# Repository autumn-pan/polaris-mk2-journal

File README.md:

# Lepton Rocket
The Lepton Rocket is a TVC rocket that is capable of guiding itself using its thruster, as well as vertical landing using a second thruster. It requires no parachute or fins and is capable of self-stabilization using only gimballed motors and lands propulsively.

# Motivation
Our motivation for building this rocket stems from a deep passion for model rocketry and a will to learn and improve through this project. Building such a complicated rocket not only helps us learn and grow as people but also pushes technological boundaries we face today with innovative new solutions. Every step, from Kalman filters to thrust vectoring, offers unique challenges that serve as learning experiences. We hope that our work will go on to support other aspiring rocketeers through open sourcing and tutorials. Moreover, we are testing new methods of reversing exhaust jets and are testing materials in extreme environments. We hope that this research will inspire other projects that can make a real impact.

# Design

PCB

WIRING

CAD

# CAD Files
View the CAD files in ./cad, or preferably in the onshape document
[Link](https://cad.onshape.com/documents/b936ec593d2f13f8b4301d6a/w/959d82f8ce1a388125efc6ac/e/d0e27454aa34d56363c8f698)
# BOM -- Total Cost: $288.5, $307.25 after tax
| Name                          | Cost   | Link                                                                                                                                                                                                                                                                                                                                                      | Purpose                                           |
|-------------------------------|--------|------------------------------------------------------------------------------------------------------------------------------------------------------------------------------------------------------------------------------------------------------------------------------------------------------------------------------------------------------------|---------------------------------------------------|
| Teensy 4.1                    | 35.49  | [Link](https://www.amazon.com/PJRC-Cortex-M7-Processor-iMXRT1062-Without/dp/B088JY7P2H/ref=asc_df_B088JY7P2H?mcid=8ae789eb80d63b429a8b6233ef5751e7&hvocijid=17548775748303405856-B088JY7P2H-&hvexpln=73&tag=hyprod-20&linkCode=df0&hvadid=730312820598&hvpos=&hvnetw=g&hvrand=17548775748303405856&hvpone=&hvptwo=&hvqmt=&hvdev=c&hvdvcmdl=&hvlocint=&hvlocphy=9001697&hvtargid=pla-2281435177898&psc=1) | Processing information and running code          |
| Bosch Sensortec BMI088                        | 5.23   | [Link](https://www.digikey.com/en/products/detail/bosch-sensortec/BMI088/8634936)                                                                                                                                                                                                                                 | Reading inertial data                            |
| Bosch Sensortec BMP390                        | 3.15   | [Link](https://www.digikey.com/en/products/detail/bosch-sensortec/BMP390/16164577)                                                                                                                                                                                                                               | Reading altitude                                 |
| 2 WAGOs  (2601-1104)                     | 8.72   | [Link](https://www.digikey.com/en/products/detail/wago-corporation/2601-1104/17123797?gQT=1)                                                                                                                                                                                                                     | Connecting pyro channels                         |
| XT30U connector                        | 0.72   | [Link](https://www.tme.eu/en/details/xt30upb-m/dc-power-connectors/amass/?utm_source=octopart.com&utm_medium=cpc&utm_campaign=compare-2025-05-27)                                                                                                                                                                 | Connecting the battery                           |
| 8x Servo Pins    (G800W305018EU)         | 7.84   | [Link](https://www.digikey.com/en/products/detail/amphenol-icc-commercial-products-/G800W305018EU/13683151?gQT=1)                                                                                                                                                                                                 | Connecting the servo pins                        |
| 5x DMN1019UVT-7                     | 4.10   | [Link](https://www.digikey.com/en/products/detail/diodes-incorporated/DMN1019UVT-7/5126835)                                                                                                                                                                                                                       | Controlling pyro channels                        |
| Printed Circuit Board         | 50.00  | [Link](https://jlcpcb.com/)                                                                                                                                                                                                                                                                                       | Mounting flight computer devices on. We only ask that you pay for printing, shipping, and taxes on the raw circuit boards. We will try to fund the resistors, capacitors, etc. ourselves             |
| 3ml Syringes                  | 2.93  | [Link](https://www.aliexpress.us/item/3256806328171497.html?spm=a2g0o.productlist.main.1.413b734d9NaMbA&aem_p4p_detail=2025073016395111874069278487360002035883&algo_pvid=8ce5ca76-1fcf-42fd-9431-eb7cfd16bba9&algo_exp_id=8ce5ca76-1fcf-42fd-9431-eb7cfd16bba9-0&pdp_ext_f=%7B%22order%22%3A%22832%22%2C%22eval%22%3A%221%22%7D&pdp_npi=4%40dis!USD!2.60!2.60!!!18.56!18.56!%40210313e917539187916456686eafd5!12000037489056984!sea!US!0!ABX&curPageLogUid=oJgz2mSzbKY4&utparam-url=scene%3Asearch%7Cquery_from%3A&search_p4p_id=2025073016395111874069278487360002035883_1)                                                                                                                                                                                                                                                                        | Dampening landing legs                           |
| Brushless Motor               | 0.99   | [Link](https://www.aliexpress.us/item/3256806626806030.html?)                                                                                                                                                                                                                                                     | Driving the reaction wheel                       |
| Extension Cable               | 5.99   | [Link](https://www.amazon.com/FLY-RC-Connector-Extension-Brushless/dp/B0B12CFKNZ/ref=asc_df_B0B12CFKNZ?mcid=8e5db81149053e17aedeaeb54fc6da1f&hvocijid=2611908650921179939-B0B12CFKNZ-&hvexpln=73&tag=hyprod-20&linkCode=df0&hvadid=721245378154&hvpos=&hvnetw=g&hvrand=2611908650921179939&hvpone=&hvptwo=&hvqmt=&hvdev=c&hvdvcmdl=&hvlocint=&hvlocphy=9001697&hvtargid=pla-2281435177618&th=1) | Connecting the motor to the flight computer      |
| Set Screws 50pc 2cm 5mm       | 1.38   | [Link](https://www.aliexpress.us/item/2251832795980382.html?spm=a2g0o.productlist.main.11.4816cYVfcYVfrL&algo_pvid=4b71b07a-a4f2-45ce-9069-14c906ecce58&algo_exp_id=4b71b07a-a4f2-45ce-9069-14c906ecce58-10&pdp_ext_f=%7B%22order%22%3A%22403%22%2C%22eval%22%3A%221%22%7D&pdp_npi=4%40dis%21USD%211.35%211.15%21%21%211.35%211.15%21%402101ea8c17477554416392859edc7d%2166712359808%21sea%21US%210%21ABX&curPageLogUid=z28QujZoM2cn&utparam-url=scene%3Asearch%7Cquery_from%3A) | Weighing down the reaction wheel                |
| 1/4 acetyl copolymer rods-- 4 3ft rods and 8 2ft rods| 36.91 | https://buyplastic.com/delrin-acetal-copolymer-plastic-rod/ | Landing legs and supporting the fuselage
|2 servos bms127wv+| 54.97|[link](https://www.redwingrc.com/product.php?productid=2746)| Pricy, but very necessary due to the high forces that they will be subjected to. These are for tvc
| 2 servos PTK 7462W MG| 19.44 | https://www.aliexpress.us/item/3256807624830309.html? | Thrust reversal system
| TSP563200DDCR | 0.90 | https://www.digikey.com/en/products/detail/texas-instruments/TPS563200DDCR/5034343 | converting the battery to a lower voltage for the teensy to handle
| 5x 300 Ohm Resistor RC0402JR-07300RL| 0.50 | https://www.digikey.com/en/products/detail/yageo/RC0402JR-07300RL/726461 | Managing MOSFET gates
| 7x 10k Ohm Resistor RC0402JR-0710KL| 0.70 | https://www.digikey.com/en/products/detail/yageo/RC0402JR-0710KL/726418 | Pull down resistors for MOSFETS
| 4x 4.7k Ohm Resistor RC0402JR-074K7L | 0.50 | https://www.digikey.com/en/products/detail/yageo/RC0402JR-074K7L/726477 | Sensor stack pull down resistors
| 1x 55k Ohm Resistor ERA-2AEB563X| 0.10 | https://www.digikey.com/en/products/detail/panasonic-electronic-components/ERA-2AEB563X/1706047 | Managing TSP563200 output voltage
| 7x 0.1 uF Capacitor CL05B104KP5NNNC | 0.56 | https://www.digikey.com/en/products/detail/samsung-electro-mechanics/CL05B104KP5NNNC/3886660 | smoothing voltage
| 2x 22 uF Capacitor | 0.05 | https://www.digikey.com/en/products/detail/murata-electronics/GRM188R61A226ME15D/5027561 | Smoothing voltage with the TSP
| F15-0 Estes Rocket Motor| 22.95 | https://fusionscalehobbies.com/products/estes-f15-0-29mm-engines-2pk?variant=44043735826688&country=US&currency=USD&utm_medium=product_sync&utm_source=google&utm_content=sag_organic&utm_campaign=sag_organic&utm_campaign=gs-2022-04-29&utm_source=google&utm_medium=smart_campaign&gad_source=1&gad_campaignid=17519716778&gbraid=0AAAAAoZqEGAQWxo04MMDcF5MdhRO7ZtAf&gclid=Cj0KCQjwhafEBhCcARIsAEGZEKLQsLOV6peTK6vGFhD8sOgo2fjzVBQZQKSE6nMh4wYBtARwmmqMCWkaAuOZEALw_wcB | Launching the rocket |
|Solder paste | 4.36 | https://www.aliexpress.us/item/3256809207808464.html? | soldering SMDs to the PCB |
| Threaded inserts | 1.73 | https://www.aliexpress.us/item/3256803396040989.html? | TVC assembly |
| Bearings | 6.26 | https://www.aliexpress.us/item/3256802138888272.html? | TVC Assembly |
| 5x Threaded acrew | 7.05 | https://www.aliexpress.us/item/3256806603708402.html? | General connections |
| Insert Nuts | 4.98 | https://www.aliexpress.us/item/3256808011211144.html? | General connections |

Notes on our vendors:
- Teensy 4.1 is necessary for its high speed, reliability, and ease of use. It is necessary for advanced avionics like this project. However, it's difficult to optimize the price of, and the cheapest price from a trusted vendor was about $31. Considering free shipping however, the cheapest vendor was on Amazon and was $35. Aliexpress was thoroughly considered and while vendors there were considered, they were found to be misleading and/or untrustworthy. A bad MPU is not only a waste of money and time, but can also be a violation of safety guidelines.
- The acetyl copolymer rods are the cheapest and most reliable on the market for what they are-- we thoroughly checked. Aliexpress does not offer any rod long enough to support this rocket, and has insufficient quality assurance which could compromise the safety of this project. Also note that this is including shipping for a large object, which is absolutely necessary in this case. Alternative rocket bodies can cost upwards of $90 at this size, so this really is the cheapest possible. Furthermore, we considered carbon fiber rods from aliexpress, however we were not allowed to purchase them in the quantity that we needed, and even the cheapest rods from Aliexpress did not make a significant difference. We really optimized the rods and rocket body to the extreme.
- We looked on Aliexpress for banana extender cables, but all options were either more expensive or significantly too short for what we needed. The one on amazon is the cheapest one that works.
- The servos we found are the only servos strong enough that can fit inside the rocket. Any larger servos could introduce significant problems during flight. These are also necessary because it is for a guidance system, and therefore needs to be fast and respond quickly. We found the cheapest servos possible.
- The servos for thrust reversing can be cheaper, so we got the cheapest servos from Aliexpress that are still strong enough to do their job. This cut costs by upwards of $40. The servos could not be cheaper than this.
- We were promised that Hack Club would supply one pack of Estes F15-0 motors by Acon

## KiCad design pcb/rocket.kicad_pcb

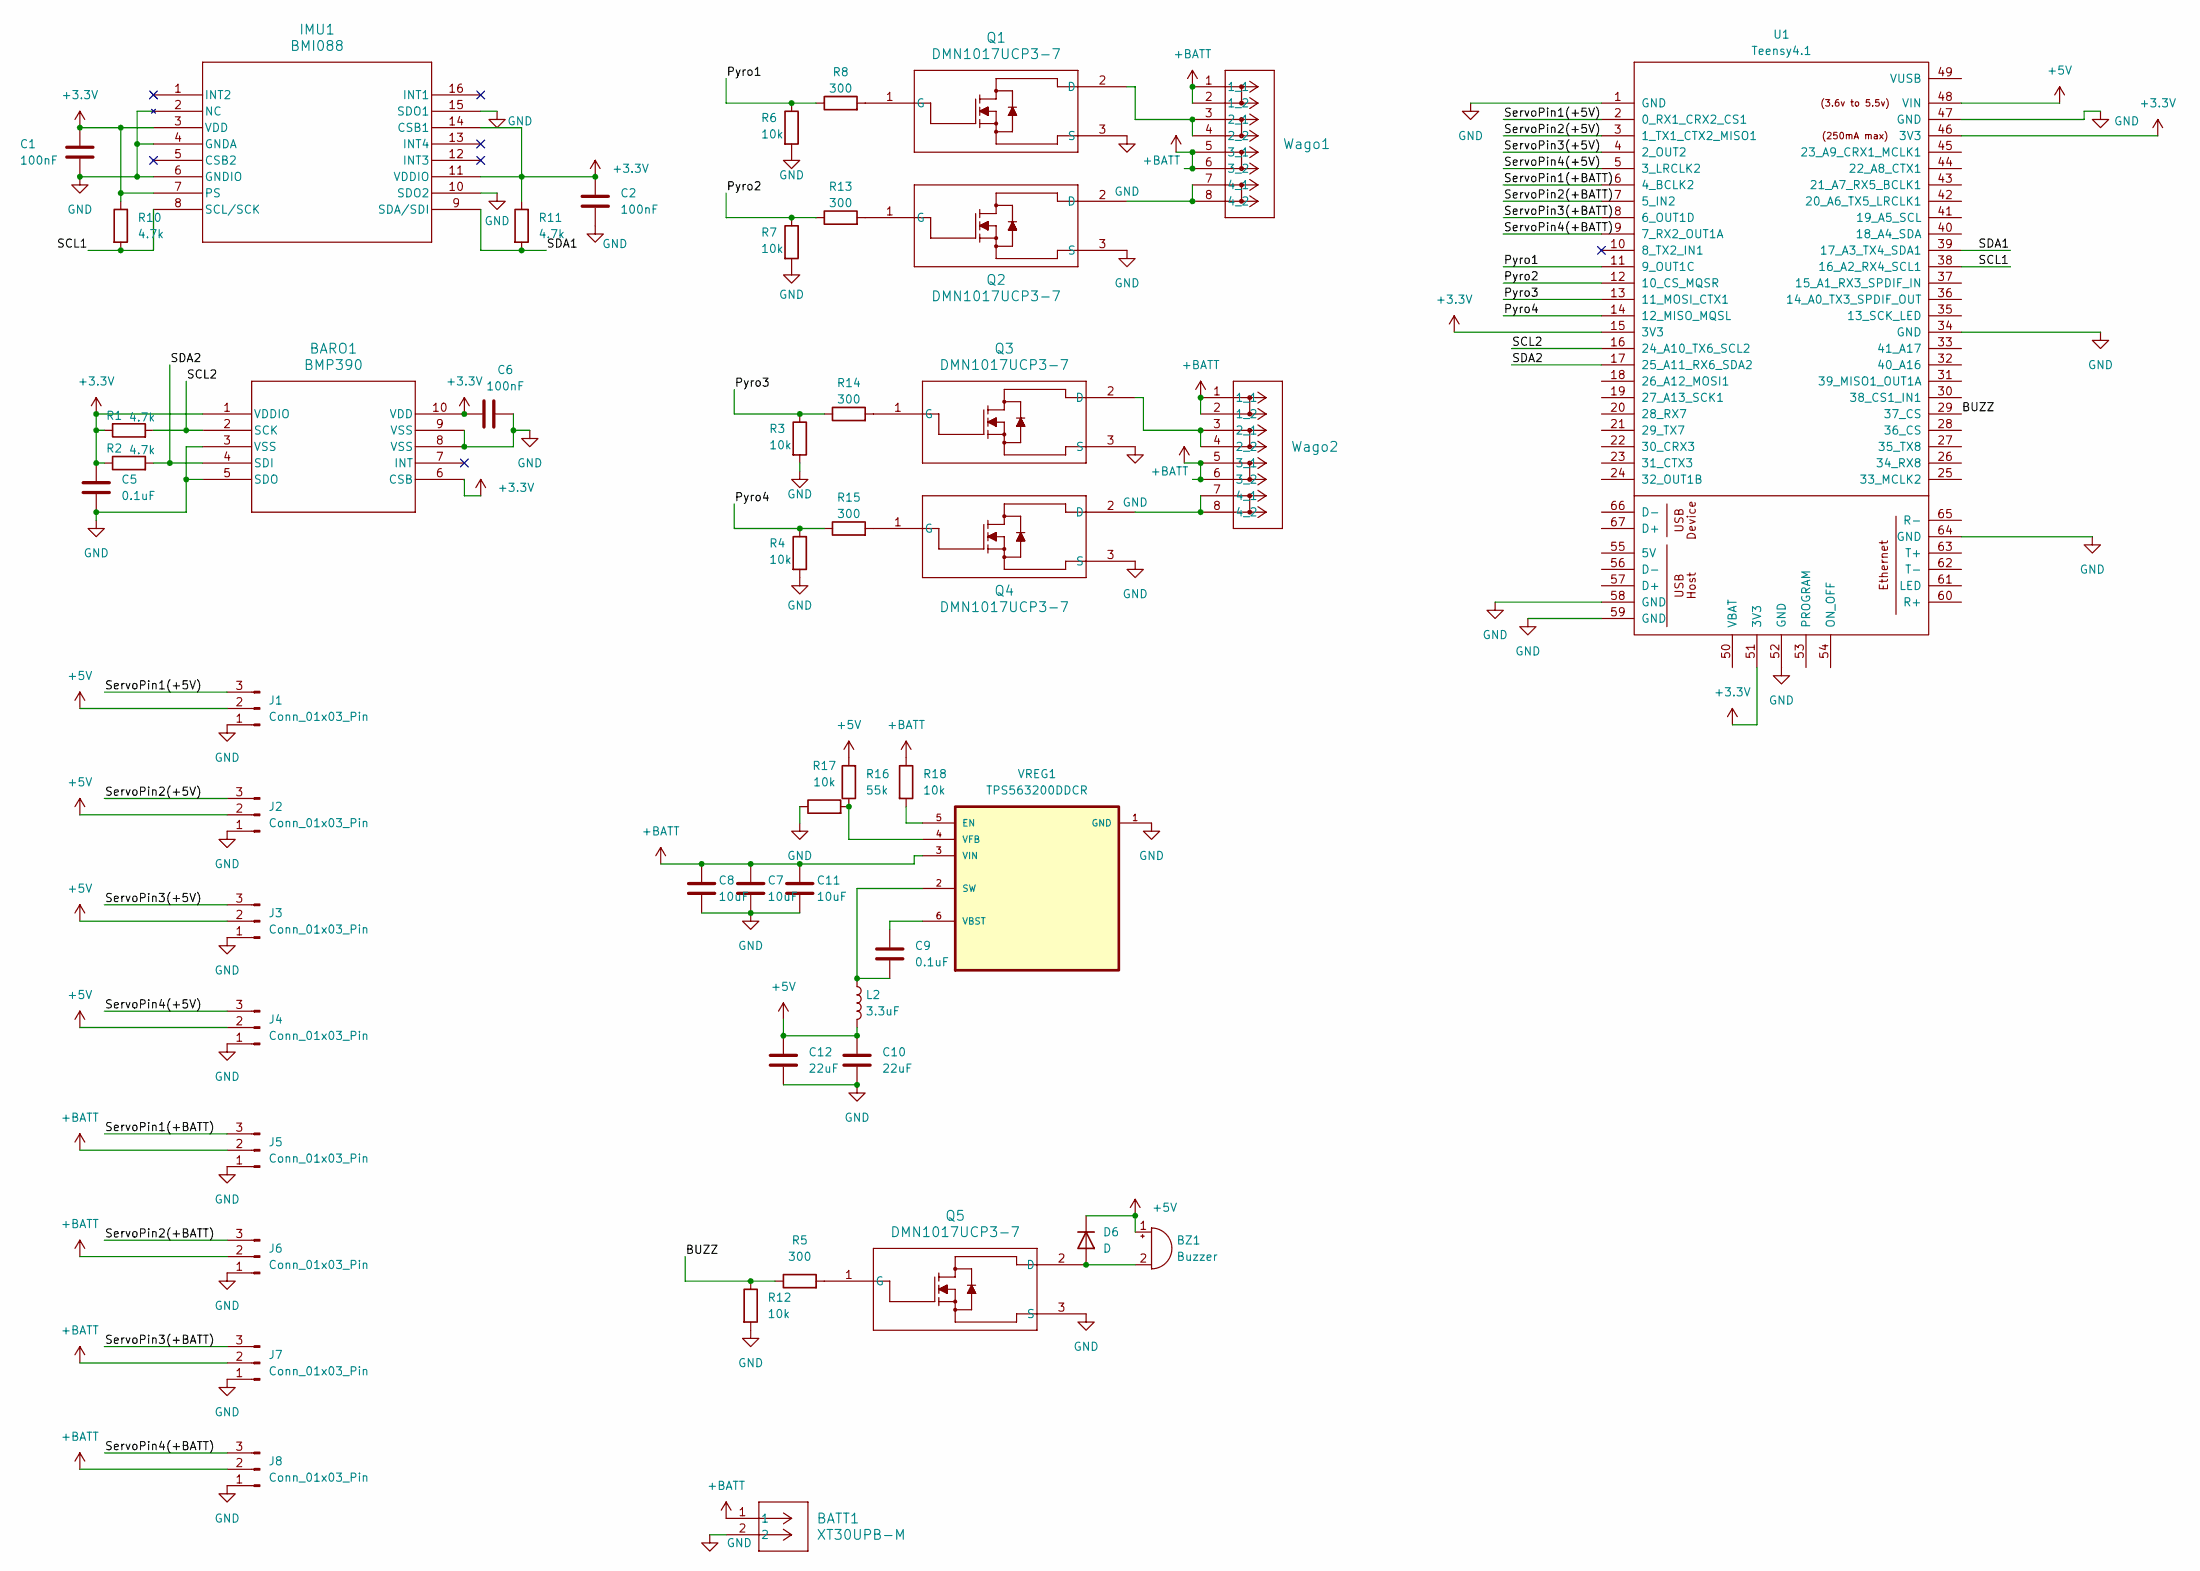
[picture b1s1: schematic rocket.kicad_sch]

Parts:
BARO1: BMP390; 10LGA_2X2X0p75_BOS
BATT1: XT30UPB-M; CONN_XT30UPB-M_AMA
BZ1: Buzzer; CEM-1206S_CUD
C1, C2, C6: 100nF; C_0805_2012Metric
C5, C9: 0.1uF; C_0805_2012Metric
C7, C8, C11: 10uF; C_0805_2012Metric
C10, C12: 22uF; C_0805_2012Metric
D6: D; D_0805_2012Metric
IMU1: BMI088; QFN_BMI085_BOS
J1, J2, J3, J4, J5, J6, J7, J8: Conn_01x03_Pin; PinHeader_1x03_P2.54mm_Vertical
L2: 3.3uF; IND_NRS5030_TAY
Q1, Q2, Q3, Q4, Q5: DMN1017UCP3-7; X3-DSN1010-3_DIO
R1, R2, R10, R11: 4.7k; R_0805_2012Metric
R3, R4, R6, R7, R12, R17, R18: 10k; R_0805_2012Metric
R5, R8, R13, R14, R15: 300; R_0805_2012Metric
R16: 55k; R_0805_2012Metric
U1: Teensy4.1; Teensy41
VREG1: TPS563200DDCR
Wago1, Wago2: 2601-1104; CONN4_2601-1104_WAG

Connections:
+3.3V: BARO1.1 (VDDIO), BARO1.6 (CSB), BARO1.10 (VDD), C1.1, C2.1, C5.1, C6.2, IMU1.3 (VDD), IMU1.7 (PS), IMU1.11 (VDDIO), IMU1.14 (CSB1), R1.1, R2.1, R10.1, R11.1, U1.15 (3V3), U1.46 (3V3), U1.51 (3V3)
+5V: BZ1.1 (+), C10.2, C12.2, D6.1 (K), J1.2, J2.2, J3.2, J4.2, L2.2, R16.2, U1.48 (VIN)
+BATT: BATT1.1, C7.1, C8.1, C11.1, J5.2, J6.2, J7.2, J8.2, R18.1, VREG1.3 (VIN), Wago1.1 (1_1), Wago1.2 (1_2), Wago1.5 (3_1), Wago1.6 (3_2), Wago2.1 (1_1), Wago2.2 (1_2), Wago2.5 (3_1), Wago2.6 (3_2)
/BUZZ: R5.1, R12.1, U1.29 (37_CS)
/Pyro1: R6.1, R8.1, U1.11 (9_OUT1C)
/Pyro2: R7.1, R13.1, U1.12 (10_CS_MQSR)
/Pyro3: R3.1, R14.1, U1.13 (11_MOSI_CTX1)
/Pyro4: R4.1, R15.1, U1.14 (12_MISO_MQSL)
/SCL1: IMU1.8 (SCL/SCK), R10.2, U1.38 (16_A2_RX4_SCL1)
/SCL2: BARO1.2 (SCK), R1.2, U1.16 (24_A10_TX6_SCL2)
/SDA1: IMU1.9 (SDA/SDI), R11.2, U1.39 (17_A3_TX4_SDA1)
/SDA2: BARO1.4 (SDI), R2.2, U1.17 (25_A11_RX6_SDA2)
/ServoPin1(+5V): J1.3, U1.2 (0_RX1_CRX2_CS1)
/ServoPin1(+BATT): J5.3, U1.6 (4_BCLK2)
/ServoPin2(+5V): J2.3, U1.3 (1_TX1_CTX2_MISO1)
/ServoPin2(+BATT): J6.3, U1.7 (5_IN2)
/ServoPin3(+5V): J3.3, U1.4 (2_OUT2)
/ServoPin3(+BATT): J7.3, U1.8 (6_OUT1D)
/ServoPin4(+5V): J4.3, U1.5 (3_LRCLK2)
/ServoPin4(+BATT): J8.3, U1.9 (7_RX2_OUT1A)
GND: BARO1.3 (VSS), BARO1.5 (SDO), BARO1.8 (VSS), BARO1.9 (VSS), BATT1.2, C1.2, C2.2, C5.2, C6.1, C7.2, C8.2, C10.1, C11.2, C12.1, IMU1.2 (NC), IMU1.4 (GNDA), IMU1.6 (GNDIO), IMU1.10 (SDO2), IMU1.15 (SDO1), J1.1, J2.1, J3.1, J4.1, J5.1, J6.1, J7.1, J8.1, Q1.3 (S), Q2.3 (S), Q3.3 (S), Q4.3 (S), Q5.3 (S), R3.2, R4.2, R6.2, R7.2, R12.2, R17.1, U1.1 (GND), U1.34 (GND), U1.47 (GND), U1.52 (GND), U1.58 (GND), U1.59 (GND), U1.64 (GND), VREG1.1 (GND)
unnamed: BZ1.2 (-), D6.2 (A), Q5.2 (D)
unnamed: Q1.2 (D), Wago1.3 (2_1), Wago1.4 (2_2)
unnamed: Q1.1 (G), R8.2
unnamed: Q2.2 (D), Wago1.7 (4_1), Wago1.8 (4_2)
unnamed: Q2.1 (G), R13.2
unnamed: Q3.2 (D), Wago2.3 (2_1), Wago2.4 (2_2)
unnamed: Q3.1 (G), R14.2
unnamed: Q4.2 (D), Wago2.7 (4_1), Wago2.8 (4_2)
unnamed: Q4.1 (G), R15.2
unnamed: Q5.1 (G), R5.2
unnamed: R18.2, VREG1.5 (EN)
unnamed: C9.2, L2.1, VREG1.2 (SW)
unnamed: C9.1, VREG1.6 (VBST)
unnamed: R16.1, R17.2, VREG1.4 (VFB)

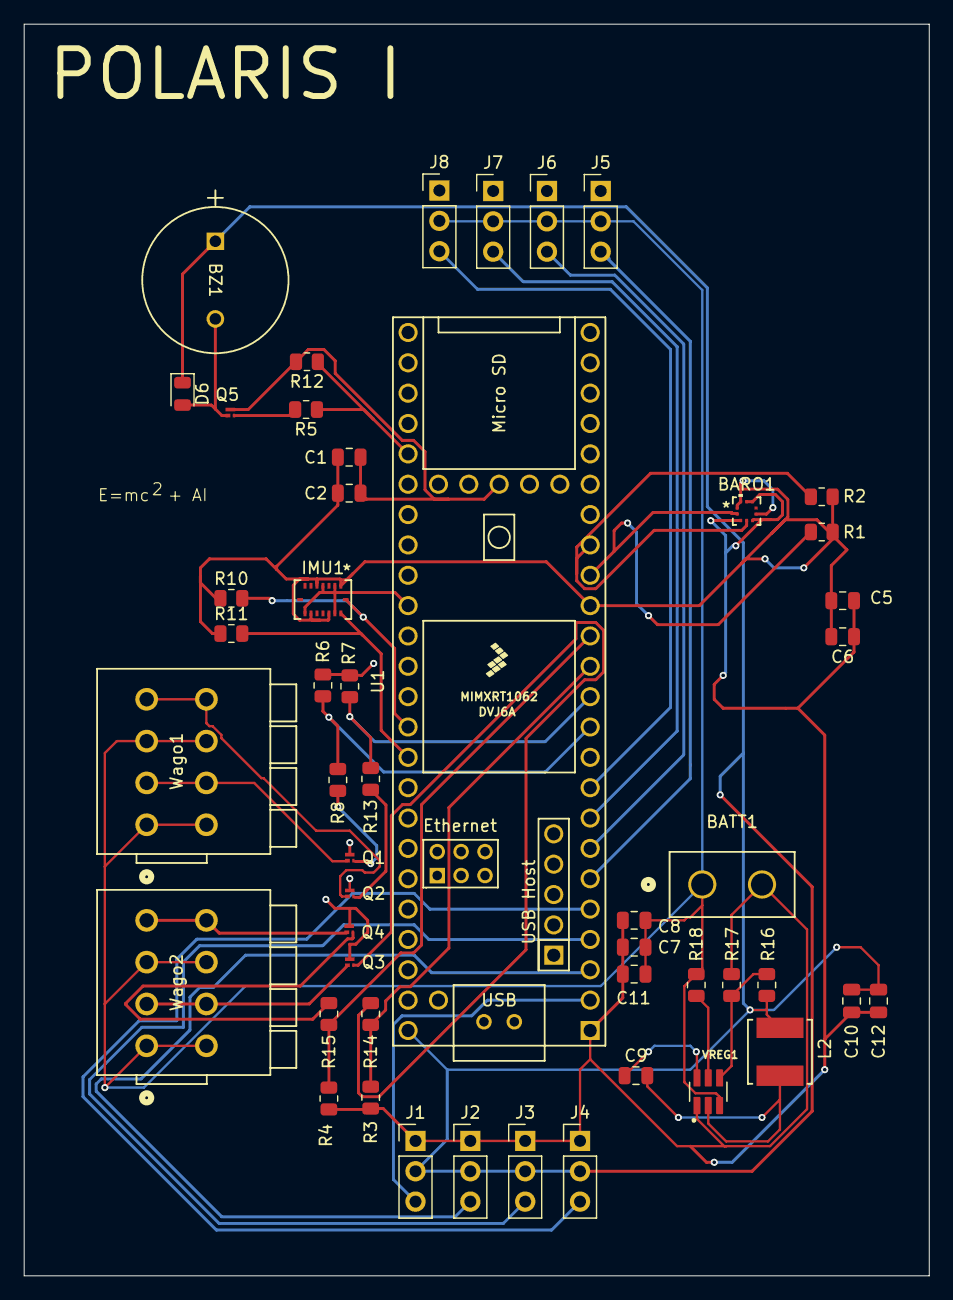
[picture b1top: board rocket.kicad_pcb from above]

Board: 2 copper layers, 75.8 x 104.8 mm, 50 parts (0 on the bottom side), 35 nets.

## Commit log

2025-05-30 init files
2025-05-30 add first few days
2025-06-01 add new day
2025-06-02 add day 9
2025-06-03 add day 10
2025-07-19 add more days
2025-07-20 add day 31
2025-07-20 add day 0
2025-07-22 add readme
2025-07-22 fix bom
2025-07-22 add kicad files
2025-07-23 add markdown bom
2025-07-23 move markdown bom
2025-07-23 add cad journal
2025-07-23 add cad image
2025-07-23 fix cad and pcb images
2025-07-23 add acetyl copolymer rods to bom
2025-07-23 add rods to bom
2025-07-23 add BOM cost
2025-07-23 add cad
2025-07-23 add servos
2025-07-23 fix hours
2025-07-23 specify hours
2025-07-24 add autumn
2025-07-24 oops
2025-07-24 dox him
2025-07-24 fix start date
2025-07-24 update bom
2025-07-24 add tax
